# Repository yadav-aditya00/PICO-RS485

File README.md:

# PICO-RS485
# MSPM0 Custom PCB Design

This repository contains the complete design files for a **custom MSPM0-based embedded PCB** designed using **KiCad**.  
The project includes schematic design, PCB layout, routing files, and supporting documentation required to manufacture the board.

The PCB is designed with a compact layout and optimized component placement suitable for embedded and IoT applications.

---

## Project Overview

This project demonstrates the complete workflow of **custom PCB design**, starting from schematic capture to PCB layout and final fabrication files.

The design includes:
- MSPM0 microcontroller based system
- Power supply circuitry
- Passive components and decoupling capacitors
- Custom component placement
- Compact PCB layout
- Design rule checks (DRC/ERC)
- Routing and board optimization

The PCB layout and component placement can be seen in the project documentation. :contentReference[oaicite:0]{index=0}

---

## Tools Used

- **KiCad PCB Design Suite**
- PCB Editor
- Schematic Editor
- Design Rule Check (DRC)
- Electrical Rule Check (ERC)

---

## Repository Structure

---

## Key Features

- Compact PCB design
- Optimized component placement
- Efficient routing strategy
- Proper decoupling for stable power delivery
- Ready for fabrication

---

## Applications

This type of PCB design can be used in:

- Embedded systems
- IoT devices
- Microcontroller-based applications
- Hardware prototyping

---

## How to Open the Project

1. Install **KiCad**
2. Clone this repository
3. Open `MSPM0_PROJECT.kicad_pro`
4. View schematic in **Schematic Editor**
5. View PCB layout in **PCB Editor**

---

## Author

**Aditya Kumar Singh**  
B.Tech Electronics & Communication Engineering (VLSI)  
IIIT Manipur  

---

## License

This project is shared for **educational and research purposes**.

---

## Hashtags

#PCBDesign  
#KiCad  
#EmbeddedSystems  
#HardwareDesign  
#Microcontroller  
#ElectronicsEngineering  
#IoT  
#OpenHardware  
#EngineeringProjects

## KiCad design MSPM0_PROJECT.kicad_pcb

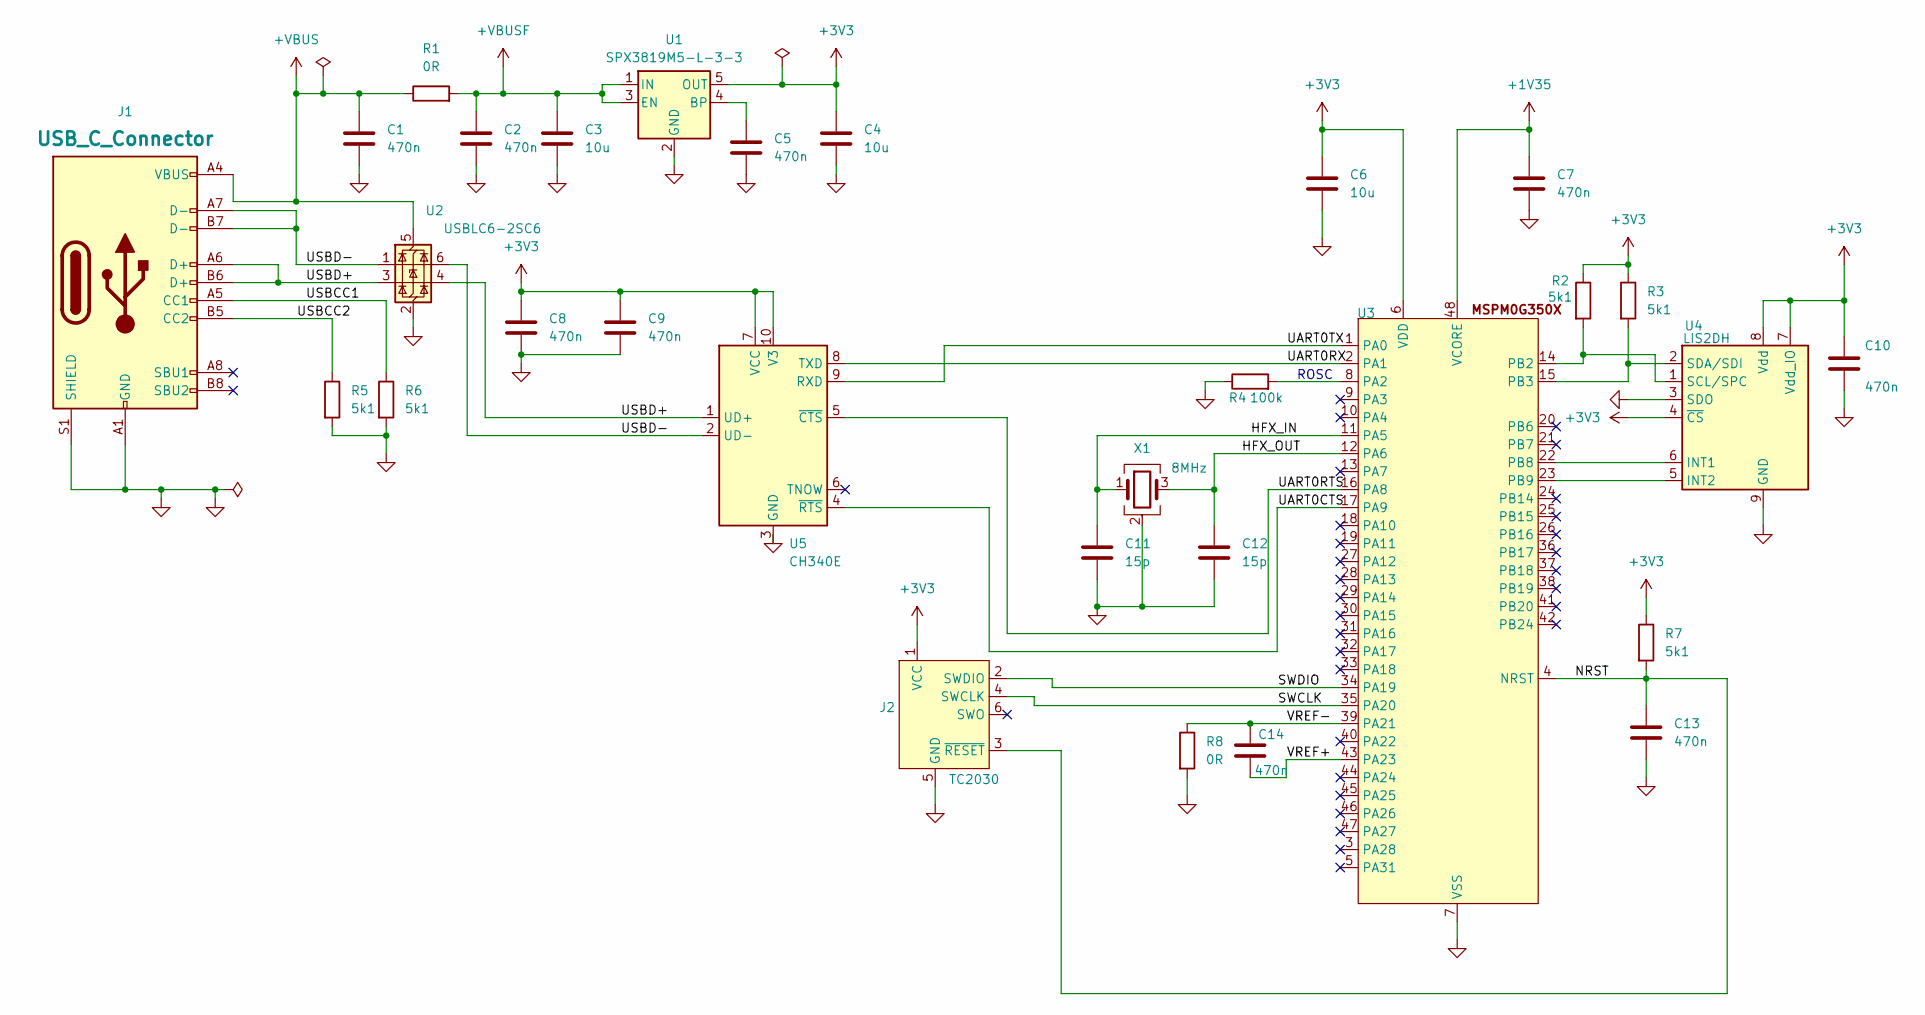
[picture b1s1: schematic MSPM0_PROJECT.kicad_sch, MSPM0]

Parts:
C1, C2, C5, C7, C8, C9, C10, C13, C14: 470n; C_0603_1608Metric
C3, C4, C6: 10u; C_01005_0402Metric
C11, C12: 15p; C_0603_1608Metric
J1: USB_C_Connector; USB_C_Receptacle_GCT_USB4105-xx-A_16P_TopMnt_Horizontal
J2: TC2030; Tag-Connect_TC2030-IDC-FP_2x03_P1.27mm_Vertical
R1, R8: 0R; R_0201_0603Metric
R2, R3, R5, R6, R7: 5k1; R_0201_0603Metric
R4: 100k; R_0201_0603Metric
U1: SPX3819M5-L-3-3; SOT-23-5
U2: USBLC6-2SC6; SOT-23-6
U3: MSPM0G3507SPTR; LQFP-48_7x7mm_P0.5mm
U4: LIS2DH; LGA-14_2x2mm_P0.35mm_LayoutBorder3x4y
U5: CH340E; MSOP-10_3x3mm_P0.5mm
X1: 8MHz; Crystal_SMD_3225-4Pin_3.2x2.5mm_HandSoldering

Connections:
+1V35: C7.1, U3.48 (VCORE)
+3V3: C4.1, C6.1, C8.1, C9.1, C10.1, J2.1 (VCC), R2.1, R3.1, R7.1, U1.5 (OUT), U3.6 (VDD), U4.4 (~CS), U4.7 (Vdd_IO), U4.8 (Vdd), U5.7 (VCC), U5.10 (V3)
+VBUS: C1.1, J1.A4 (VBUS), J1.A9 (VBUS), J1.B4 (VBUS), J1.B9 (VBUS), R1.1, U2.5 (VBUS)
+VBUSF: C2.1, C3.1, R1.2, U1.1 (IN), U1.3 (EN)
/HFX_IN: C11.1, U3.11 (PA5), X1.1
/HFX_OUT: C12.1, U3.12 (PA6), X1.3
/NRST: C13.1, J2.3 (~RESET), R7.2, U3.4 (NRST)
/SWCLK: J2.4 (SWCLK), U3.35 (PA20)
/SWDIO: J2.2 (SWDIO), U3.34 (PA19)
/UART0CTS: U3.17 (PA9), U5.4 (~RTS)
/UART0RTS: U3.16 (PA8), U5.5 (~CTS)
/UART0RX: U3.2 (PA1), U5.8 (TXD)
/UART0TX: U3.1 (PA0), U5.9 (RXD)
/USBCC1: J1.A5 (CC1), R6.1
/USBCC2: J1.B5 (CC2), R5.1
/USBD+: J1.A6 (D+), J1.B6 (D+), U2.3 (I/O2), U2.4 (I/O2), U5.1 (UD+)
/USBD-: J1.A7 (D-), J1.B7 (D-), U2.1 (I/O1), U2.6 (I/O1), U5.2 (UD-)
/VREF+: C14.2, U3.43 (PA23)
/VREF-: C14.1, R8.1, U3.39 (PA21)
GND: C1.2, C2.2, C3.2, C4.2, C5.2, C6.2, C7.2, C8.2, C9.2, C10.2, C11.2, C12.2, C13.2, J1.A1 (GND), J1.A12 (GND), J1.B1 (GND), J1.B12 (GND), J1.S1 (SHIELD), J2.5 (GND), R4.1, R5.2, R6.2, R8.2, U1.2 (GND), U2.2 (GND), U3.7 (VSS), U4.3 (SDO), U4.9 (GND), U5.3 (GND), X1.2 (G), X1.4 (G)
unnamed: C5.1, U1.4 (BP)
unnamed: R4.2, U3.8 (PA2)
unnamed: R2.2, U3.14 (PB2), U4.1 (SCL/SPC)
unnamed: R3.2, U3.15 (PB3), U4.2 (SDA/SDI)
unnamed: U3.22 (PB8), U4.6 (INT1)
unnamed: U3.23 (PB9), U4.5 (INT2)
unnamed: U4.10 (GND), U4.11 (GND), U4.12 (GND), U4.13 (GND), U4.14 (GND)

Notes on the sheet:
ROSC

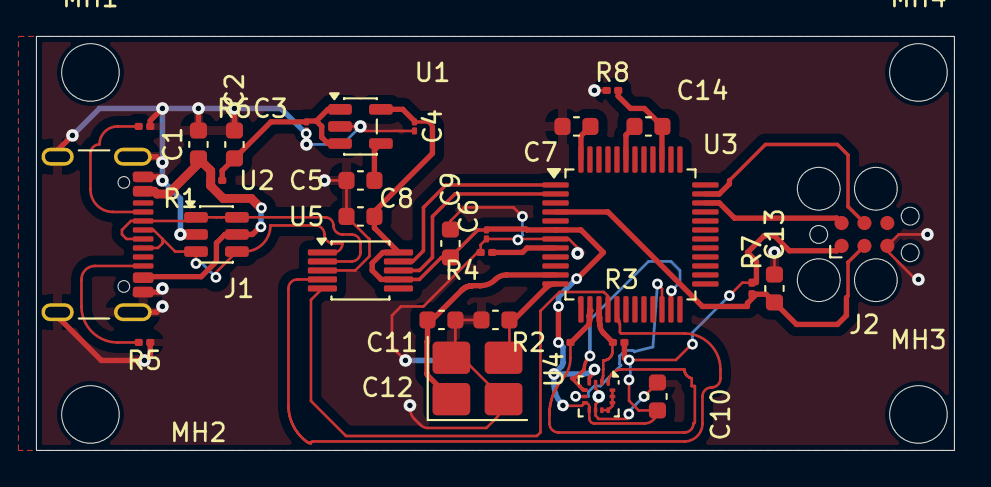
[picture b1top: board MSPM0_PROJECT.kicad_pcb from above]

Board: 2 copper layers, 51.0 x 23.0 mm, 34 parts (0 on the bottom side), 27 nets.

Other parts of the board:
MH1, MH2, MH3, MH4: M3; MountingHole_3.2mm_M3

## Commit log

2026-03-13 Revise README for MSPM0 Custom PCB project
    Updated README to provide detailed project information including overview, tools used, key features, applications, and instructions for opening the project.
2026-03-13 Add MSPM0 custom PCB design files created in KiCad
